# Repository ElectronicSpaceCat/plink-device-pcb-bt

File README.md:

# plink-device-pcb-bt

The primary pcb has the bluetooth module (where the firmware resides).

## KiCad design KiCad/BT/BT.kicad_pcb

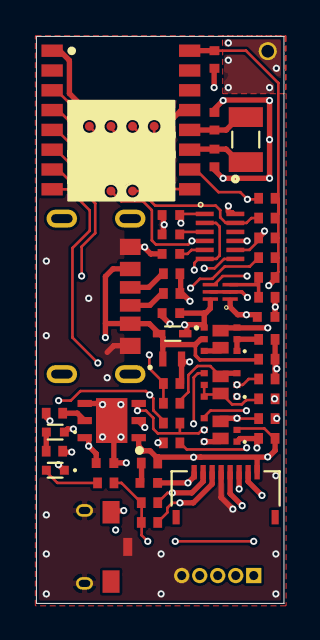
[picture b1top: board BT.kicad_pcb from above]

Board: 4 copper layers, 13.8 x 31.5 mm, 50 parts (0 on the bottom side), 39 nets.

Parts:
C1, C2, C5, C6, C10: 1uF; Capacitor_Taiyo_Yuden_0402
C3, C4: 4.7uF; Capacitor_Taiyo_Yuden_0402
C7: 0.22uF; Capacitor_Taiyo_Yuden_0402
C8, C9: 7pF; Capacitor_Taiyo_Yuden_0402
CR1: ESDA7P60-1U1M; ESDA7P601U1M
D1: BAT30KFILM
D2: YEL/GRN; led_QBLP595
D3: ORG; led_QBLP595
J1: UJC-HP-3-SMT-TR; CUI_UJC-HP-3-SMT-TR
J2: 2328702-8; TE_2328702-8
J3: Conn_01x05; PinHeader_1x05_P1.00mm_Vertical
R1, R2: 5.1k (5%); Stackpole_Res_0402
R3: 75k (1%); Stackpole_Res_0402
R4: 30k (1%); Stackpole_Res_0402
R5: 12.5k; Stackpole_Res_0402
R6, R9, R10, R20, R21: 10k; Stackpole_Res_0402
R7: 1.0; Stackpole_Res_0402
R8: 10k (1%); Stackpole_Res_0402
R11, R12, R13, R14, R16, R22, R23, R24: 100k; Stackpole_Res_0402
R15: 75k; Stackpole_Res_0402
R17, R18, R19: 4.7k; Stackpole_Res_0402
SW1: PTS840ESDPMSMTRLFS
U1: LDK130PU-R
U2: STBC08PMR; SON95P300X300X100-7N-D
U3: STM6601CQ2BDM6F; STM6601AQ2BDM6F
U4: BC832; XCVR_BC832
U5, U6, U7: SSM6L61NU
Y1: ECS-.327-7-34R-TR; XTAL_ECS-.327-7-34R-TR

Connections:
BM: R14.2, R15.1, U4.9
BM_EN: R16.1, U4.D2, U6.2
CHRG: D3.1, R12.2, U2.3, U3.7, U7.5
CHRG_STAT: R22.2, U4.C2, U7.3, U7.7
EN: U1.4, U3.9
GND: C1.2, C2.2, C3.2, C4.2, C5.2, C6.2, C7.2, C8.2, C9.2, C10.2, CR1.2, J1.A12, J1.B12, J2.5, J2.8, J3.5, R1.2, R2.2, R4.2, R11.2, R15.2, R16.2, R22.1, R23.1, R24.2, SW1.3, SW1.4, SW1.5, U1.2, U1.5, U2.4, U2.7, U3.12, U4.1, U6.1, U7.1
INT: R9.2, U3.11, U4.C5
unnamed: C4.1, R7.2
unnamed: C6.1, U3.3
unnamed: C7.1, U3.5
unnamed: C8.1, U4.11, Y1.1
unnamed: C9.1, U4.12, Y1.2
unnamed: D2.1, U4.8
unnamed: D2.2, R19.2
unnamed: D3.2, R5.2
unnamed: J1.A5, R1.1
unnamed: J1.B5, R2.1
unnamed: R3.1, R4.1, U1.3
unnamed: R8.2, U2.5
unnamed: R13.1, U6.5, U6.6, U6.8
unnamed: R14.1, U6.3, U6.7
unnamed: R24.1, U5.1, U5.2
unnamed: SW1.1, U3.2, U3.6
unnamed: U5.6, U5.8
PB_OUT: R10.2, U3.8, U4.13
PROG: R8.1, U7.6, U7.8
PS_HOLD: R20.2, U3.4, U4.B5
PWR_ON: R6.2, U2.2, U4.5
RESET: J3.2, R21.2, U4.10
SCL: J2.7, R17.1, U4.7
SDA: J2.6, R18.1, U4.6
SWDCLK: J3.4, U4.4
SWDIO: J3.3, U4.3
V2.8: C2.1, C10.1, J2.2, J3.1, R3.2, R6.1, R9.1, R10.1, R17.2, R18.2, R19.1, R20.1, R21.1, U1.1, U4.16, U7.4
VBATT: J2.1, R7.1, R13.2, R23.2, U2.1, U5.3, U5.7, U6.4, U7.2
VBUS: C1.1, C5.1, D1.2, R5.1, R12.1, U1.6, U3.1, U5.4
VUSB: C3.1, CR1.1, D1.1, J1.A9, J1.B9, R11.1, U2.6, U5.5
XSHUT1: J2.4, U4.A2
XSHUT2: J2.3, U4.B2

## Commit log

2023-02-25 Update LICENSE

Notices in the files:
parts and their libraries:
Copyright 2016 Accelerated Designs. All rights reserved.
